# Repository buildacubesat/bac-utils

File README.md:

# bac-utils

Build a CubeSat – the utilities that keep the project running: KiCad release and library tooling, antenna simulation, Blender video editing helpers, media conversion, content and resource pipelines, repository checks, and the business operations suite. Every tool follows the [BAC Project & Tooling Guide](https://buildacubesat.space) and the BAC Interface Design Guide, so they look and behave alike: the same flags, the same terminal output, the same config locations.

The repository holds the generally usable state of each tool. Anything specific to one project – vendor prices, sheet IDs, repository paths, plugin locations – lives in your own config and data directories, created by each tool's `--init`. What ships here is the tool, sample data under `examples/`, and an `.env.example` where secrets are involved. See §6 to adapt a tool for your own project.

## 1. Tools

This table is the record of what exists, what is being worked on and what is planned; an available tool's name links to its directory: **available** has a tool directory, tests and a version; **in progress** has a directory on a branch or a concept note and work under way; **planned** has a decided home here and nothing built yet. Tools are listed by name within their group: libraries, command-line tools (with the one Tk window and the gallery), notebooks, the web app, the operations suite, the Blender extension.

| Tool | Type | Domain | What it does | Status | Version |
| :-- | :-- | :-- | :-- | :-- | :-- |
| [`bac-common`](lib/bac-common/) | library | CLI scaffold | Shared CLI scaffold: standard flags, TOML config, `.env` loading, `--init` helpers, the BAC terminal profile, error boundary, span-preserving s-expression parser, STEP header metadata, the part-catalog reader and resolver, Google Sheets reader (`gsheets` extra), test harness | available | v0.5.0 |
| [`bac-kicad-common`](lib/bac-kicad-common/) | library | KiCad | Shared KiCad library tooling: TOML field rules, property rendering for KiCad 9 and 10, span edits, write-back with backup | available | v0.1.0 |
| [`bac-suite-db`](lib/bac-suite-db/) | library | ops | Shared PostgreSQL layer of the operations suite: `bac.items` and `bac.catalog`, bootstrap config and the DSN in `.env`, the SKU scheme as a parser, an engine registry, the `bac-db` command (migrate, import, export, status) | available | v0.1.1 |
| [`bac-antenna-optimizer`](tools/bac-antenna-optimizer/) | CLI | RF | Antenna design around openEMS: parametric geometry, meshing rules, band targets, cavity-model pre-tuner, tolerance sweeps, sensitivity packs, reports with drawings, charts and KiCad board files | available | v0.7.5 |
| [`bac-brand-assets`](tools/bac-brand-assets/) | CLI | design | The construction of the BAC marks – the isometric cube symbol, the Nunito wordmark, the horizontal logo – and the generator that writes them as black, white and `currentColor` SVG into bac-design's `assets/`, with the trademark notice in every file, plus the tagline logo, the badges and the Rocinante marks, and their PNG and WebP renderings; `--check` in CI | available | v0.2.0 |
| [`bac-cad-preview`](tools/bac-cad-preview/) | CLI | CAD | Renders STEP, STL and 3MF files to 720 px WebP previews framed like the KiCad artifacts render, with an X/Y/Z scale gizmo; the preview stage of the planned `bac-freecad-generate-artifacts` | available | v0.5.1 |
| [`bac-can-up`](tools/bac-can-up/) | CLI | bench | Brings up the CANable SLCAN interface: fresh `slcand`, bitrate, `can0` up | available | v1.2.0 |
| `bac-catalog` | CLI | store | Builds the static part catalog the builder reads from the `part.toml` files next to the hardware designs | planned | – |
| [`bac-convention-check`](tools/bac-convention-check/) | CLI | repo | Lints a tree against the BAC guides (typography, naming, licensing, packaging, flags); runs in this repository's CI | available | v0.2.2 |
| [`bac-csr-ingest`](tools/bac-csr-ingest/) | CLI | resources | Ingests documents and links into the CubeSat Resources site: extraction, LLM classification, review, upload, index, commit | available | v0.4.1 |
| [`bac-design-export`](tools/bac-design-export/) | CLI | design | Exports the BAC guides in bac-design from Markdown to PDF as BAC documents (Identity Guide §7.3): markdown-it and WeasyPrint, the tokens straight from `bac-design-tokens`, the self-hosted fonts, A4 or Letter, contents and running header and footer; `--check` compares a source hash in each PDF, `--format html` shows the page in a browser |
| [`bac-design-tokens`](tools/bac-design-tokens/) | CLI | design | The canonical BAC design tokens (`tokens.json`, W3C design-tokens format) and the generator that writes every copy from them: the gallery's and the suite's `tokens.css`, the Rich colours in `bac-common`, the marimo style cells and chart constants; `--check` in CI | available | v0.1.0 |
| `bac-freecad-generate-artifacts` | CLI | CAD | FreeCAD counterpart of the KiCad artifacts tool: exports the file types and iterations of a part through the FreeCAD CLI, renders previews (absorbs `bac-cad-preview`), fills missing author, organisation and part metadata in STEP and 3MF output | planned | – |
| [`bac-issue-print`](tools/bac-issue-print/) | CLI | repo | Prints a Codeberg issue or pull request with its whole timeline – comments, reviews, pushes, references – as Markdown | available | v0.2.0 |
| [`bac-kicad-generate-artifacts`](tools/bac-kicad-generate-artifacts/) | CLI | KiCad | Produces the release bundle for a KiCad project through kicad-cli: render, pinout, schematic PDF, BOM – thin or legacy scheme; with the part catalogs configured also dev and flight build BOMs, a JLCPCB assembly file and an issues list –, iBOM, a frozen project with one build's parts written in, Gerbers, drills, centroid, STEP with header metadata, QR code on a copy of the board, manufacturing ZIP; panels without a schematic | available | v0.8.0 |
| [`bac-kicad-hlabels`](tools/bac-kicad-hlabels/) | CLI | KiCad | Emits hierarchical-label blocks for a list of net names, ready to paste into a schematic | available | v0.1.0 |
| [`bac-kicad-libcheck`](tools/bac-kicad-libcheck/) | CLI | KiCad | Verifies a library project: every symbol and footprint placed once, 3D models resolvable, in sync per KiCad's ERC/DRC | available | v0.2.0 |
| [`bac-kicad-maintain`](tools/bac-kicad-maintain/) | CLI | KiCad | Project files on the conventions: text and courtyard sizes on boards, via resizing, schematic label sizes, the title block's company, library nickname renames, size statistics; the library audit – unused footprints and models, broken links, field mismatches – with `#unused-` prefixing; the catalog check with the README tables regenerated | available | v1.4.1 |
| [`bac-kicad-schfields`](tools/bac-kicad-schfields/) | CLI | KiCad | Bulk-edits symbol fields and flags across a schematic hierarchy from TOML rules | available | v0.2.1 |
| [`bac-kicad-stitch`](tools/bac-kicad-stitch/) | CLI | KiCad | Ground stitching vias where a board's ground copper is too far from one: coverage by pitch or frequency, every spot checked against copper, holes, edge and courtyards on all layers, vias added by span in a `bac-stitch` group, preview SVG, DRC afterwards | available | v0.1.1 |
| [`bac-kicad-symfields`](tools/bac-kicad-symfields/) | CLI | KiCad | Fills fields, lints and fixes text sizes and footprint references in symbol and footprint libraries, preserving file formatting | available | v0.3.1 |
| [`bac-markdown-to-youtube`](tools/bac-markdown-to-youtube/) | CLI | content | Converts Markdown to YouTube description markup | available | v0.2.0 |
| [`bac-media-convert`](tools/bac-media-convert/) | CLI | media | Batch conversions: square WebP for the store, constant-frame-rate MP4 from variable-rate WebM | available | v0.1.1 |
| [`bac-page`](tools/bac-page/) | CLI | web | Creates and manages bac.page short URLs: a redirect folder per slug in the Pages repository, committed and pushed; `list`, `edit` (slug, destination), QR codes in SVG, PNG or WebP; a renamed slug stays as an alias of the new one | available | v0.6.0 |
| [`bac-reference-gallery`](tools/bac-reference-gallery/) | CLI and pages | design | Seven design-reference boards for the three BAC guides (identity, Ops and Mission, documents, interface patterns, charts, hardware, a product sheet) in light and dark, `tokens.css` (written by `bac-design-tokens`) as the stylesheet they are built on, a renderer to PNG and PDF through a headless Chromium, and `--serve` to show the pages in any browser | available | v0.5.0 |
| [`bac-store-product-cropper`](tools/bac-store-product-cropper/) | Tk GUI | media | Framing product photos for the store by hand, one window per batch, each crop exported as WebP under a size target; may later fold into a store artifact-generation tool | available | v0.2.1 |
| [`bac-update-content-plan`](tools/bac-update-content-plan/) | CLI | content | Renders the content plan from a Google Sheet into the docs repository as one Markdown table; commits and pushes on request | available | v0.4.1 |
| [`bac-antenna-visualizer`](notebooks/bac-antenna-visualizer/) | marimo notebook | RF | A slider per geometry parameter over an optimizer sensitivity pack: S-parameters, Smith chart, gain and axial ratio, pattern cuts, 3D pattern and fields; runs locally, with a frozen demo snapshot under `demo/` that runs in the browser from the repository and fetches its packs there | available | v0.3.8 |
| `bac-battery-pack` | marimo notebook | power | Battery pack configuration (cell, S × P, depth of discharge, temperature) and aging: cycle and calendar capacity fade over the mission, usable energy at end of life, the pack figures the power budget takes | planned | – |
| [`bac-link-budget`](notebooks/bac-link-budget/) | marimo notebook | RF | Link budget for a CubeSat radio link: passes, margins, data volume per day, validated against the AMSAT/IARU link model and SGP4 | available | v0.7.7 |
| [`bac-optical-payload`](notebooks/bac-optical-payload/) | marimo notebook | optics | Earth-observation and boom-camera optics: GSD, swath, smear, access and illumination over a target, days to downlink | available | v0.7.7 |
| `bac-orbit-viewer` | marimo notebook | orbit | 3D view of a mission's geometry around the globe from any sibling's profile | planned | – |
| [`bac-orbital-lifetime`](notebooks/bac-orbital-lifetime/) | marimo notebook | orbit | Decay under drag with NRLMSIS 2.1 and ten solar-activity scenarios; lifetime against launch date; disposal rules | available | v0.2.8 |
| [`bac-power-budget`](notebooks/bac-power-budget/) | marimo notebook | power | Generation, storage and loads over the orbit with a scheduler and safe mode | available | v0.5.7 |
| `bac-pv-aging` | marimo notebook | power | Single-diode model of a solar cell string fitted to datasheet points and aged over the mission by UV, atomic oxygen, displacement damage and thermal cycling: BOL and EOL IV curves, the EOL power factor the power budget takes | planned | – |
| `bac-thermal` | marimo notebook | thermal | Lumped-parameter thermal model of the spacecraft over the orbit, hot and cold cases, battery heater energy | planned | – |
| `bac-builder` | web app | store | Web app to configure a CubeSat build from BAC parts with a 3D view, tied to the store's prices and stock; cart, quote, CSV and PDF outputs; mass, power and data budgets per build | planned | – |
| [`bac-pricing`](ops/bac-pricing/) | marimo notebook | ops | Assembly pricing: multi-level BOM cost rollup and batch-waterfall price derivation as a pure engine, the notebook over it, the `pricing` schema of the operations suite; `bac-pricing` opens the notebook on the configured backend | available | v1.4.3 |
| [`bac-suite`](ops/bac-suite/) | CLI | ops | The operations suite's orchestrated shell: one web app with every installed engine's notebook behind a common index | available | v0.2.2 |
| [`bac-vse-tools`](blender/bac-vse-tools/) | Blender extension | video | One extension with three sub-panels in the VSE sidebar: bulk import of a folder of clips end to end, proxies built one strip at a time, meta strips separated with their trim kept | available | v1.0.0 |

The guides the tools follow – Identity, Interface Design, Project & Tooling and the Trademark Policy – live in [bac-design](https://github.com/buildacubesat/bac-design).

## 2. Install

Each tool is its own `uv` project and installs independently:

```sh
uv tool install ./tools/bac-issue-print
bac-issue-print --init
```

Tools that build on `bac-common` install from the checkout, not from PyPI; after pulling a new version, `uv tool install --force --reinstall ./tools/<name>` replaces the installed one. A tool with an optional extra takes it in the path: `uv tool install './tools/bac-cad-preview[step]'`. The suite's command-line tools install together – `uv tool install ./lib/bac-suite-db --with ./ops/bac-pricing` gives `bac-db` with the pricing engine – and `ops/README.md` describes the group. The reference gallery renders through a headless Chromium; `bac-reference-gallery --init` finds one or downloads Playwright's, and `bac-reference-gallery --serve` shows the pages in your browser (a Flatpak or Snap browser cannot open them from disk with their folder). The antenna optimizer runs inside the workspace environment because it needs the openEMS bindings (its README has the setup), and the notebooks run through marimo (§3).

The Blender extension is installed from a zip of `blender/bac-vse-tools/src/bac_vse_tools/` through Preferences → Get Extensions → Install from Disk; its README has the two ways to build the zip.

To work on the repository itself:

```sh
uv sync --all-packages
uv run pytest
uv run ruff check .
```

## 3. Notebooks

The engineering notebooks under `notebooks/` – link budget, optical payload, power budget, orbital lifetime, and the local-only antenna visualizer (with a frozen demo snapshot that runs on molab) – are single marimo files with PEP 723 metadata. Run one in its own environment with `uvx marimo edit --sandbox notebooks/bac-link-budget/bac_link_budget.py`, or in the workspace environment with `uv run marimo edit <file>`. The four published ones are the files behind the bac.page links, which open them from this repository's `main` – `bac.page/molab-<tool>-app` in app mode on marimo.app, ready to use, `bac.page/molab-<tool>` as a notebook in molab's editor – so a merge publishes; each of them carries the shipped profiles as TOML files under `examples/` and headless regression tests. The BAC profiles assume the 500 km planning orbit. `notebooks/README.md` has the rules of the class.

## 4. Layout

```
lib/       shared libraries (bac-common, bac-kicad-common, bac-suite-db)
notebooks/ engineering notebooks (marimo, single files, published for the community)
tools/     one directory per CLI tool, installable with uv tool install; the antenna optimizer's
           simulation output (runs/) stays out of git and the kept runs live in bac-hardware
ops/       business operations suite (Marimo notebooks + PostgreSQL)
blender/   Blender extensions
```

Every tool directory has the same shape: `pyproject.toml`, `src/bac_<name>/cli.py`, `README.md` with a version history, `tests/`, and where the tool consumes data, `examples/`. The reference gallery adds its pages beside them (`index.html`, `css/`, `assets/`, `examples/`), and the wheel carries them inside the package.

## 5. Conventions

Every CLI tool built on `bac-common` prints `<tool> vX.Y.Z` for `-v/--version`, accepts a hidden `--debug` that shows tracebacks, and keeps `--help` within 48 lines (24 until 2026-11-05) including two or three examples (at the end; the older Typer tools – `bac-csr-ingest`, `bac-kicad-symfields`, `bac-media-convert` – still print them above the options). The other standard flags appear where they apply: `--dry-run` where a run writes or changes something (on the subcommand that does, for the tools with subcommands), `--init` where the tool has a first-time setup – settings to write, or a browser to fetch for the reference gallery – and `--config PATH` where it keeps persistent settings, `--env-file PATH` where it reads secrets or machine-specific values, `-l/--list` where it works on a named set. Filters that write to stdout (`bac-markdown-to-youtube`, `bac-kicad-hlabels`) and read-only tools (`bac-convention-check`) have no `--dry-run`. Each tool's README lists its flags. Since 0.7.5 the antenna optimizer's command line is on `bac-common` too (it predated the scaffold); its subcommands keep their own plain tables. The notebooks are exempt from the flags and carry their version in `TOOL_VERSION` and in every export's header.

Config lives at `~/.config/bac/<tool>.toml`; secrets in a `.env` file loaded with python-dotenv. Exit codes are 0 for success, 1 for a runtime error, 2 for bad arguments. Errors go to stderr; tracebacks appear only with `--debug`. Terminal output uses the BAC Interface Design Guide's terminal profile through `bac_common.ui`. Colours, type and form come from one place, `tools/bac-design-tokens/src/bac_design_tokens/tokens.json`: `bac-design-tokens` writes them into the gallery's and the suite's `tokens.css`, the Rich colours and the notebooks' style cells, and its tests fail when a copy is stale.

Software in this repository is licensed MIT (see `LICENSE`); documentation CC BY-SA 4.0. The design tokens (`tokens.json`) and the reference gallery's stylesheets are both – MIT or CC BY-SA 4.0, at your option – so any software, BAC Ground included, can take the values. The Build a CubeSat name and logo are not covered by this repository's licenses; see the [BAC Trademark Policy](https://github.com/buildacubesat/bac-design/blob/main/guides/bac-trademark-policy.md). Software versions follow SemVer and display with a `v` prefix.

## 6. Adapting for your own project

Run `<tool> --init`. It asks for the paths, identifiers and endpoints the tool needs, writes `~/.config/bac/<tool>.toml`, and where secrets are involved, a `.env` next to your working directory with empty values to fill in. Tools that consume data files take a data directory from that config; the copies under each tool's `examples/` show the expected shape and can be copied as a starting point. Nothing in the repository needs editing to point a tool at your own project.

## 7. Version history

| Version | Date | Change |
| :-- | :-- | :-- |
| 0.24.1 | 2026-11-06 | `bac-kicad-maintain` v1.4.1: the audit compares `Description` only for symbols that name a part, and a live symbol nothing places is not reported when a catalog row names its part. |
| 0.24.0 | 2026-11-05 | `bac-kicad-generate-artifacts` v0.8.0: the BOM scheme (`thin` default, `legacy` for projects whose symbols carry their part data – no catalog, `--bom-scheme`), the `Build` and `Qty per footprint` fields, the `freeze` stage (`--freeze dev|flight` writes `<project>-frozen-<build>/` with the resolved part numbers in every symbol and footprint, DNP on build-excluded parts, `FROZEN.md`), the iBOM on KiCad's DNP attribute. `bac-common` v0.5.0: `bac_common.catalog` (the reader and resolver moved from the artifacts tool, the third collection named `other`, `check()` and the README tables) and the help limit at 48 lines. `bac-kicad-maintain` v1.4.0: `check`/`apply --catalog` (findings on the catalog CSVs, the ICs-shaped READMEs regenerated), `[audit] catalogs` on `resources/catalog/`. `bac-kicad-symfields` v0.3.1 and `bac-kicad-schfields` v0.2.1: the example rules retired as the BAC workflow. |
| 0.23.0 | 2026-11-05 | `bac-kicad-maintain` v1.3.0: the library audit as `check`/`apply --audit` over a repository root – the central library, every board, sheet, template and design block, the catalog CSVs – reporting unused footprints and 3D models (the usage rule of 2026-10-29), broken links with `#unused` hints, field mismatches and unplaced symbols; `apply` prefixes unused files `#unused-` and lets the references in unused symbols and footprints follow. `--titleblock` sets the title block's company (`nihil.space GmbH`) on boards and sheets. `uv.lock` caught up with `bac-reference-gallery` 0.5.2. |
| 0.22.0 | 2026-10-29 | New `bac-design-export` v0.1.0: the guide PDFs in bac-design `exports/` built Markdown → HTML → PDF as BAC documents, per the new Identity Guide §7.3 – the tokens from `bac-design-tokens` (no copy), static Nunito Sans instances cut from the variable font and IBM Plex Mono embedded, a BAC Symbols face for the arrows and box drawing Nunito Sans lacks, contents with page numbers, `--check` by source hash. Replaces the pandoc → docx → LibreOffice route. `bac-convention-check` v0.2.3: U1 allows `bac-design` and `bac-ops` on GitHub. `bac-reference-gallery` v0.5.1: the slogan "Space for everyone." on the identity overview. `bac-brand-assets` templates: the slides template v1r2 on the Mission surfaces of the Tooldance media kit (`nebula.jpg`, paper wells, timeline, quote); `surfaces.py` renders the viewport only. |
| 0.21.0 | 2026-10-29 | `bac-page` v0.6.0: a rename leaves the old slug redirecting to the new short URL, marked as renamed in its `index.html`; `list` dims these aliases and `list --old` shows only them; `edit` and `add` leave them alone. The legacy `~/.config/bac-page/.env` is no longer read. |
| 0.20.2 | 2026-10-29 | `bac-kicad-generate-artifacts` v0.7.2: a part the catalog marks `accepted` – no qualified variant, fitted to flight builds by decision – stays in the flight build like a qualified one; `aec-q102` counts as qualified. |
| 0.20.1 | 2026-10-28 | `bac-kicad-generate-artifacts` v0.7.1: a third catalog folder, `parts`, for connectors, switches, LEDs and the like (the ICs' columns and rules); from the first live BOM of the MCU carrier, where every passive and IC resolved. |
| 0.20.0 | 2026-10-28 | `bac-kicad-generate-artifacts` v0.7.0: the `bom` stage resolves the schematic against the Build a CubeSat part catalogs (`bac-hardware/resources/`, named in `[catalog]`) – passives by value and package, ICs by manufacturer part number through their slot's flight candidate and its compatibility – and writes `…-bom-dev.csv`, `…-bom-flight.csv`, `…-bom-jlcpcb.csv` and `…-bom-issues.csv` next to the plain export; the schematic stays thin. Without `[catalog]` nothing changes. |
| 0.19.0 | 2026-10-28 | `bac-page` v0.5.0 moves in from the Pages repository's `cli/` as `tools/bac-page` on `bac-common`: the standard parser and error boundary, opening panel and summary, the shared config loader, 36 tests on a throwaway repository with a bare remote; commands, slugs, redirect files, QR options and git behaviour unchanged (a malformed slug or target exits 2 now, a subcommand's `--help` reaches the subcommand). The legacy `~/.config/bac-page/.env` is read with a note until 0.6. |
| 0.18.0 | 2026-10-27 | `bac-brand-assets` v0.2.0 (0.1.0 the same day): the BAC marks at v4r1 as a construction – the symbol a true 30° isometric 2U cube (edge 200, stroke 15, rounded corners, the dot in the 1:√3 projection ratio) on a 400 × 650 canvas, the wordmark Nunito 350 outlined with fontTools, the logo the horizontal lockup at 70 % of the cube height – written as black, white and `currentColor` SVG with title, desc and Dublin Core metadata into bac-design's `assets/`, from the Nunito that bac-design now self-hosts in `fonts/`; `--check` for CI; the logo with tagline, the symbol and logo badges, and the Rocinante marks at v2r1 from the Krita vector layers, with PNG and WebP renderings at 512 and 2048 px. The v3r1 symbol was a bitmap trace. |
| 0.17.0 | 2026-10-27 | Design 1.0: the BAC guides move to the BAC Ground console language (Identity Guide 1.0, Interface Design Guide 1.0, Project & Tooling Guide 0.15), and the tokens get one source. New `bac-design-tokens` v0.1.0: `tokens.json` and the generator for the gallery's and the suite's `tokens.css`, the Rich colours in `bac-common` and the marimo style cells and chart constants, with `--check` in its tests. `bac-reference-gallery` v0.5.0: every board on the new tokens and component language (Nunito Sans body, mono labels at 0.03em, pills, no shadows, the five states with shapes, the neutral dark-mode accent, the nebula triad). `bac-common` v0.4.2: success `#3FB950`, error `#E94538`. `bac-suite` v0.2.2: the index page on the new tokens. Notebooks – Nunito Sans body, the console surfaces and the shared chart palette, no number changes: `bac-link-budget` v0.7.7, `bac-optical-payload` v0.7.7, `bac-power-budget` v0.5.7, `bac-orbital-lifetime` v0.2.8, `bac-antenna-visualizer` v0.3.8 (demo re-snapshotted), `bac-pricing` v1.4.3 (no price changes). Colour constants on the new palette: `bac-store-product-cropper` v0.2.1, `bac-kicad-stitch` v0.1.1, `bac-cad-preview` v0.5.1. |
| 0.16.2 | 2026-10-24 | The notebooks' chart colors under marimo's "system" theme: chart text, axis lines and ticks no longer carry explicit colors – marimo hands the chart its dark theme on a dark surface and Vega's defaults apply on a light one – and the series palette is one set, the lighter nebula tints that read on a dark surface too; the style cell's `.vega-embed text` rule is gone (the charts render on canvas inside a shadow root). `bac-link-budget` v0.7.6, `bac-optical-payload` v0.7.6, `bac-power-budget` v0.5.6, `bac-orbital-lifetime` v0.2.7, `bac-antenna-visualizer` v0.3.7 (demo re-snapshotted), `bac-pricing` v1.4.2; no number changes. |
| 0.16.1 | 2026-10-24 | The follow-ups batch 1 left open. `bac-antenna-optimizer` v0.7.5: the command line on `bac-common` – `-v` prints `bac-antenna v0.7.5`, hidden `--debug`, the error boundary, `--help` within 24 lines with examples; subcommands and output unchanged. `bac-csr-ingest` v0.4.1 runs its Typer app through `run_typer` (usage errors exit 2, Ctrl-C prints `Interrupted.`). `bac-suite-db` v0.1.1: `bac-db import` on the `files` backend validates and stops with a note instead of asking for a database. `bac-kicad-generate-artifacts` v0.6.2: the `--qr` example names the live short link. `bac-convention-check` v0.2.2 knows the Pages repository's new name. CI installs Playwright's Chromium so the gallery's browser tests run, and a second workflow runs the Blender tests with the `bpy` wheel when `blender/` changes. The Pages repository is [`bac-page`](https://github.com/buildacubesat/bac-page) now; the dead `molab-antenna-viz-demo` link in the visualizer's history unlinked. |
| 0.16.0 | 2026-10-19 | `bac-kicad-stitch` v0.1.0: ground stitching vias from the filled ground zones – the pitch given or derived from a frequency, coverage instead of a via count, every candidate checked on all copper layers, farthest-point placement, the vias in a `bac-stitch` group that `remove` takes out again, a preview SVG, `kicad-cli pcb drc` after writing. |
| 0.15.2 | 2026-10-13 | `bac-issue-print` v0.2.0: the timeline instead of the plain comments – reviews with their line comments, pushes, references, title changes and the rest of what the issue page shows; `--comments-only` for the old output. |
| 0.15.1 | 2026-10-13 | `bac-issue-print` v0.1.1: the comments come in one request – the Forgejo endpoint is not paginated and 0.1.0's page walk never ended. |
| 0.15.0 | 2026-10-12 | `bac-kicad-maintain` v1.2.0, the last batch-1 tool: text, courtyard and via sizes on boards, label sizes on schematics, `stats` and `rename-library`, folded in on `bac-common` and `bac-kicad-common` with `.bak` backups, a confirmation before writing and edits that follow KiCad's line layout; boards and schematics only, footprint libraries stay with `bac-kicad-symfields fix`. |
| 0.14.1 | 2026-10-12 | The notebooks' bac.page links: two per tool, `bac.page/molab-<tool>-app` (app mode on marimo.app, ready to use) and `bac.page/molab-<tool>` (a notebook in molab's editor), both reading the file from this repository's `main` – the molab copies are gone, a merge publishes. Every intro links both; `bac-link-budget` v0.7.5, `bac-optical-payload` v0.7.5 (its short link is `molab-optical-pld` now), `bac-power-budget` v0.5.5, `bac-orbital-lifetime` v0.2.6, `bac-antenna-visualizer` v0.3.6 (the demo's short link is `molab-antenna-viz`; demo re-snapshotted). No number changes. |
| 0.14.0 | 2026-10-09 | `bac-reference-gallery` v0.4.0: `--serve` shows the gallery over `http://127.0.0.1` in any browser – opened from disk, `index.html` came up without its stylesheets and previews in a Flatpak browser, which receives a local file without its folder – and the stylesheets are dual-licensed, MIT or CC BY-SA 4.0. The notebooks' glossary links checked against the CubeSat Resources glossary (two anchors that did not exist fixed, the power rails off the deployer-rail entry, first-use links in all five) and their muted grey moved to the AA values of the shared tokens: `bac-link-budget` v0.7.4, `bac-optical-payload` v0.7.4 (its assumptions name both readings of Q, Holst's for resolution and Nyquist sampling at Q = 2, as the glossary does), `bac-power-budget` v0.5.4, `bac-orbital-lifetime` v0.2.5, `bac-antenna-visualizer` v0.3.5, and `bac-pricing` v1.4.1 for the grey; no number changes. `bac-suite` v0.2.1: the index page links `tokens.css` instead of carrying its own colours. `/tmp/` at the checkout root is ignored. |
| 0.13.0 | 2026-10-08 | `bac-reference-gallery` v0.3.0 joins on `bac-common`: the seven boards in light and dark with every colour through `tokens.css`, now the shared stylesheet and a full copy of the Identity Guide's tokens with AA-safe `--text-muted` and `--link`; every text on every board passes WCAG AA in both modes, with focus rings, reduced motion, `lang`, table scopes and labelled form controls; the product sheet without price and contact data; the renderer as `bac-reference-gallery` with `--out-dir`, `--theme`, `--source`, the pages inside the package and `--init` for the browser. `bac-common` v0.4.1 and `bac-update-content-plan` v0.4.1: the service-account key's path says where it came from. Final README pass: the tool table grouped and ordered as its intro says, §2 on installing every kind of tool, §5 states the standard flags that apply instead of claiming all of them everywhere; the notebooks' `pyproject.toml` versions follow their `TOOL_VERSION` (notebooks 0.13.0); the `bac-convention-check` row says v0.2.1 again (it read v0.2.2 since 0.8.3, a typo). The LICENSE names nihil.space GmbH and the Build a CubeSat contributors as copyright holders. |
| 0.12.0 | 2026-10-07 | `bac-vse-tools` v1.0.0: the three Blender add-ons as one extension under `blender/` with a manifest, three panels under VSE Tools and settings in a property group on the scene; Bulk Import no longer saves the open file and keeps its copies out of the media folder (autosave opt-in, confirmed) and keeps Blender's A/V sync through the Add Movie operator, the proxy build runs as a background job with a timeout over the whole wait and stale proxies ignored, Separate Meta asks before removing strips. Tested headless inside Blender 4.5 through the `bpy` wheel; `blender/` joins ruff and pytest. |
| 0.11.0 | 2026-10-07 | `bac-update-content-plan` v0.4.0 rewritten on `bac-common` (sheet, range, repository and branch in `~/.config/bac/`, the repository validated before the sheet is fetched, pipes escaped, the commit limited to the file, confirmation before `git push`, `--dry-run` reports what would change) and `bac-store-product-cropper` v0.2.0 repackaged under its new name (the double-Enter save, the stretched preview, the quality-order crash and the double listing fixed; `--out-dir`, collision check, skip of existing outputs). `bac-common` v0.4.0 adds `bac_common.gsheets` behind the `gsheets` extra. `bac-media-convert` v0.1.1: "the store" replaces "the shop" here and in its own text; the planned `bac-builder` and `bac-catalog` rows follow. |
| 0.10.0 | 2026-10-07 | The business operations suite joins under `ops/`: `bac-suite-db` v0.1.0 (the shared PostgreSQL layer lifted from bac-pricing's `bac_store.py`, `bac-db` on `bac-common`, the DSN in `.env` and redacted everywhere, the SKU scheme as a parser), `bac-pricing` v1.4.0 (engine, store and notebook as a package with the `bac-pricing` launcher, the data files as `examples/` with the three SKUs migrated to the guide scheme, the notebook on the shared style cell with one control panel, validation on import, the parity test as pytest with a guarded live variant) and `bac-suite` v0.2.0 (engines found through entry points). The SQL was run against PostgreSQL 16 before release and the live tests keep doing so with `BAC_TEST_DSN`; `ops/README.md` describes the group. |
| 0.9.1 | 2026-10-07 | `bac-kicad-generate-artifacts` v0.6.1: the output folder carries the full artifact name (`bac-inhibit-deployment-switch-v1r1/`), fixes from the first live run (absolute paths for the iBOM plugin, program lookup at call time, `--init` text). |
| 0.9.0 | 2026-10-06 | `bac-kicad-generate-artifacts` v0.6.0 joins on `bac-common`: the 0.5.0 stage architecture with the installed 0.4.2's behaviour, the live-run bugs of 2026-10-02 fixed (names from the project stem, no doubled prefix, no spaces in Gerber names, `.gbrjob` rewritten), a QR stage on `bac_common.sexp` after Emil Fresk's kicad-qr-inserter, STEP header metadata through the new `bac_common.cad` (`bac-common` v0.3.0), kicad-cli 10 targeted directly; the deployment switch and a synthetic project as fixtures. |
| 0.8.5 | 2026-10-06 | The notebooks' bac.page links are the molab short links (`bac.page/molab-<tool>`, the demo at `molab-antenna-viz-demo`); five patch bumps. |
| 0.8.4 | 2026-10-06 | `bac-orbital-lifetime` v0.2.3: the "Solar Activity Assumed" chart drew nothing in the browser since 0.1.0 (a dot in the data column name is nested access to Vega-Lite). The visualizer demo fetches its two S-band packs from `notebooks/bac-antenna-visualizer/demo/packs/` (now tracked) when none sit beside it, so a molab mirror of the file works as is. |
| 0.8.3 | 2026-10-06 | Chart titles that Altair clipped are split into title and subtitle in the five notebooks (`chart_title` in the shared chart-conventions cell): `bac-link-budget` v0.7.2, `bac-optical-payload` v0.7.2, `bac-power-budget` v0.5.2, `bac-orbital-lifetime` v0.2.2, `bac-antenna-visualizer` v0.3.3. The tool table gains a Type column and links every available tool to its directory. |
| 0.8.2 | 2026-10-06 | The BAC planning orbit moves to 500 km (was 450 km): `bac-link-budget` v0.7.1, `bac-optical-payload` v0.7.1, `bac-power-budget` v0.5.1 and `bac-orbital-lifetime` v0.2.1 with their profiles, panel defaults, regression figures and READMEs; the lifetime takes the siblings' chart-conventions and style cells; the four notebooks are formatted and linted by ruff from now on (exemptions dropped, F841 added for cell globals). |
| 0.8.1 | 2026-10-06 | `bac-antenna-visualizer`: a demo snapshot for molab under `notebooks/bac-antenna-visualizer/demo/` – the visualizer without the optimizer, geometry from the pack's stored models, packs found beside the file – with its own headless tests; the demo is covered by `marimo check` in CI. |
| 0.8.0 | 2026-10-02 | The `notebooks/` group: `bac-link-budget` v0.7.0, `bac-optical-payload` v0.7.0, `bac-power-budget` v0.5.0 and `bac-orbital-lifetime` v0.2.0 come in as byte-identical copies of the published files with example profiles and regression tests from their handoffs; `bac-antenna-visualizer` v0.3.2 moves there from `tools/`; a shared headless harness; `marimo check` and the notebook tests in CI. `bac-convention-check` v0.2.1 stops flagging a notebook's build-system-less pyproject. |
| 0.7.0 | 2026-10-02 | `bac-cad-preview` v0.5.0 joins on `bac-common`: STEP, STL and 3MF previews framed like the KiCad artifacts render, faces named with the project's axis letters, `--out-dir`, output collisions refused; the `step` extra carries OpenCascade. |
| 0.6.0 | 2026-10-02 | The two antenna tools from the S-band sessions brought in: `bac-antenna-optimizer` v0.7.4 (tag `bac-antenna-optimizer-v0.7.3` marks the version that generated the S-band cross patch in bac-hardware) and `bac-antenna-visualizer` v0.3.1, both on the conventions; the root `.gitignore` takes over their ignore rules. `bac-common` v0.2.1 and a root `conftest.py` pin the terminal widths under test, so the suite passes at any width (five tests failed at 80 columns before). The tool table becomes the tracking view of everything planned for the repository. |
| 0.5.0 | 2026-09-07 | The KiCad library tools and the CAN bench tool: `bac-kicad-symfields` v0.3.0, `bac-kicad-schfields` v0.2.0 and `bac-kicad-libcheck` v0.2.0 folded in from the separate bac-kicad-tools repository (the four `bac-kicad-misc` lint scripts absorbed as `symfields lint` and `fix`), `bac-can-up` v1.2.0 ported from `canup.sh`. New `bac-kicad-common` v0.1.0; `bac-common` v0.2.0 adds `bac_common.sexp`. All batch-1 tools have now arrived. |
| 0.4.0 | 2026-09-04 | Four small tools on the scaffold: `bac-markdown-to-youtube` v0.2.0 (rewritten conversion), `bac-issue-print` v0.1.0 (ported from shell, pagination, token), `bac-kicad-hlabels` v0.1.0 (flags, `--gap-on-blank`), `bac-media-convert` v0.1.0 (`webp-square`, `cfr`; the two shell loops retired). `bac-common` v0.1.1: `.env` is searched from the working directory, `run_typer` puts Typer tools inside the error boundary. |
| 0.3.0 | 2026-09-02 | `bac-convention-check` v0.2.0 ported to Python with TOML rule sets; runs on the repository in CI. |
| 0.2.0 | 2026-09-02 | `bac-csr-ingest` v0.4.0: first tool on `bac-common`; classifier trust boundary, upload guard, phase order. Root pytest runs in importlib mode so tools may share test module names. |
| 0.1.0 | 2026-09-02 | Repository skeleton: uv workspace, CI, `bac-common` v0.1.0 lifted from the CSR Ingest reference implementation. Tools follow in the homogenization plan's order. |

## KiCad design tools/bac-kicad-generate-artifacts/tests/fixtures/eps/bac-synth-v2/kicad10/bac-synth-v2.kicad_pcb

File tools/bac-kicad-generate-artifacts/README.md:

# bac-kicad-generate-artifacts v0.8.0

Build a CubeSat – the release bundle of a KiCad project from one command. For every project folder given, the tool drives `kicad-cli` through the stages of a hardware release and puts the results into one folder: a 720 × 720 px 3D render, a 1920 × 1080 px pinout plot, the schematic PDF, the CSV BOM – with the part catalogs configured also a dev and a flight build BOM, a JLCPCB assembly file and an issues list –, an optional interactive HTML BOM, an optional frozen project with one build's parts written in, Gerbers and Excellon drills, the pick-and-place centroid file, the STEP model with author and organisation in its header, an optional QR code on the board, and a timestamped manufacturing ZIP. Every file is named after the BAC artifact scheme `<prefix>-<subsystem>-<name>-<vXrY>-<kind>.<ext>`, with the version and revision read from the board's title block.

Everything specific to a project – output root, naming prefix, author, BOM scheme and fields, part catalogs, plugin paths – lives in `~/.config/bac/bac-kicad-generate-artifacts.toml`, written by `--init`. The defaults are BAC's; §10 says what to change for another project.

## 1. Install

```sh
uv tool install ./tools/bac-kicad-generate-artifacts   # from the bac-utils checkout
bac-kicad-generate-artifacts --init
```

Programs on `PATH` at run time: `kicad-cli` from KiCad 10 (the stages are written against the 10.x command set and tested with 10.0.3; the tool does not probe the help text for older builds) and `inkscape` or `rsvg-convert` (librsvg) to rasterise the pinout plot. The WebP images are encoded by Pillow, so `cwebp` is no longer needed. Optional: a system `python3` that imports `pcbnew`, with the InteractiveHtmlBom plugin, for `--ibom`; `xdg-open`/`open` and `gerbview` for `--open`. The tool depends on `bac-common` from this repository, so it installs from the checkout, not from PyPI.

## 2. Usage

```
bac-kicad-generate-artifacts [options] KICAD_DIR [KICAD_DIR ...]
```

```sh
bac-kicad-generate-artifacts ~/bac/bac-hardware/inhibit/deployment-switch/kicad10
bac-kicad-generate-artifacts --ibom --qr https://bac.page/deployment-switch-v1 --open deployment-switch/kicad10
bac-kicad-generate-artifacts --dry-run --skip step panel-a/kicad10 panel-b/kicad10
bac-kicad-generate-artifacts --freeze flight --only freeze ~/bac/bac-hardware/eps/main-board/kicad10
bac-kicad-generate-artifacts --bom-scheme legacy ~/nihil.space/blackwing-cm5-payload-v1/design/kicad10
```

`KICAD_DIR` is the folder that holds the `.kicad_pro`, `.kicad_pcb` and `.kicad_sch` files. Several folders are processed in turn; one failing folder does not stop the others, and the summary (projects, done, failed) is printed on every path. Exit codes: `0` every project done, `1` at least one stage or project failed, or the config file is invalid, `2` bad arguments.

| Option | Effect |
| :-- | :-- |
| `--desktop DIR` | Output root. Default: `root` in the config, else `$XDG_DESKTOP_DIR` or `~/Desktop`. |
| `--only STAGES`, `--skip STAGES` | Run only, or run without, the named stages (comma-separated; §3 has the names). An unknown name exits 2 and lists them. |
| `--ibom` | Also build the interactive HTML BOM (opt-in: it needs KiCad's own Python). |
| `--qr TEXT` | Replace the `QR_MARKER` text boxes on the board with a QR code of `TEXT` (§6). |
| `--bom-scheme SCHEME` | `thin` (the default, and `scheme` in `[bom]`): the schematic carries value, footprint and manufacturer part number and the catalogs supply the rest (§5). `legacy`: the symbols carry manufacturer, package, tolerance and the rating fields themselves – the plain export gets those columns and no catalog is read (§5.3). |
| `--freeze BUILD` | Also write the frozen project of the `dev` or `flight` build next to the project folder (§5.2). |
| `--patch N` | Patch revision on the version tags: `v1r2` becomes `v1r2.N` for the board and the schematic. |
| `--open` | Open the output folder in the file manager and the ZIP in GerbView when the project is done. |
| `--dry-run` | Print the plan and record the commands (`--debug` shows them); nothing is written, not even the output folder. The QR stage only names its text, so the recorded board paths are the project's own. |
| `--config PATH`, `--init` | Another config file; first-time setup (§4). |

The run prints an opening panel, a rule per project with the board, title, revision, schematic and output folder, one `✓` line per stage with the file it wrote, its size and the time it took (`✗` with the reason when a stage fails, `·` for a skipped stage), and the summary. `--debug` adds every command that was run and keeps the `.work/` folder.

## 3. Stages

Stages run in this order; `--only` and `--skip` pick from them.

| Stage | Writes | Notes |
| :-- | :-- | :-- |
| `qr` | `.work/project/<board>.kicad_pcb` | Opt-in (`--qr TEXT` or `text` in `[qr]`). Copies the project folder into the work folder and replaces the marker boxes on the copy; the later board stages export from that copy. The project itself is never written. |
| `render` | `<base>-render.webp` | `kicad-cli pcb render` at 2160 × 2160 px, rotated 22.5°/−22.5°, zoom 0.8, side lights at 90°, transparent; cropped to the board, padded 10 %, squared and resized to 720 px, lossless WebP. `bac-cad-preview` frames its previews the same way. |
| `schematic` | `<sch-base>-schematic.pdf` | Black and white, all sheets. |
| `pinout` | `<base>-pinout.webp` | `Edge.Cuts`, `F.Fab` and `F.Silkscreen` as a single black-and-white SVG, rasterised at 4× and scaled to 80 % of a 1920 × 1080 px transparent canvas. |
| `bom` | `<sch-base>-bom.csv`, `…-bom-dev.csv`, `…-bom-flight.csv`, `…-bom-jlcpcb.csv`, `…-bom-issues.csv` | `kicad-cli sch export bom` with the scheme's columns (or the field list, labels and grouping from `[bom]`); a `Qty per footprint` field multiplies the quantity (§5.1). In the thin scheme with the part catalogs configured in `[catalog]` (passives, ICs, other), a second export (reference, quantity, value, footprint, `Manufacturer PN`, DNP, `Build`, `Qty per footprint`) is resolved against them and written as the dev and flight build BOMs, the JLCPCB assembly file and the issues list (§5). In the legacy scheme the plain export is all there is. |
| `ibom` | `<base>-ibom.html` | Opt-in (`--ibom`). Exports a `kicadxml` netlist and runs the InteractiveHtmlBom plugin (`script` in `[ibom]`) with the first Python that imports `pcbnew`: `python` in `[ibom]`, then `/usr/bin/python3`, then `python3`. Dark mode, pin 1 highlighted, KiCad's DNP attribute as the DNP source (the `BOM` field of 0.7 is gone from the library); the plugin's browser tab opens only with `--open`. The plugin takes a relative `--dest-dir` as relative to the board's folder, so it gets absolute paths. |
| `freeze` | `<project>-frozen-<build>/` next to the project folder | Opt-in (`--freeze dev` or `--freeze flight`); needs the thin scheme and the catalogs. Copies the project folder (backups, caches and lock files left out) and writes the build's resolved `Manufacturer PN`, `LCSC` and `Digikey` into every placed symbol and board footprint; a part the `Build` field keeps out of the build gets the DNP attribute; `FROZEN.md` and two title-block comments record build, date, catalog versions and source commit (§5.2). A folder of that name is replaced. |
| `gerbers` | `gerber/` | Into an emptied `gerber/`: the board's copper layers (read from its `(layers …)` block, in stack order) plus `F.Paste`, `B.Paste`, `F.Silkscreen`, `B.Silkscreen`, `F.Mask`, `B.Mask`, `Edge.Cuts`; on a panel also `User.Comments` (V-cut lines). RS-274X without X2 attributes, 6 digits, KiCad extensions. Zone fills are exported as saved: `--check-zones` is never passed, so a panel's fills stay as the panelizer left them and a board's fills are the ones its designer last filled. |
| `drills` | `drill/` | Into an emptied `drill/`: Excellon, absolute origin, millimetres, decimal format. |
| `centroid` | `centroid/<base>-centroid.pos` | ASCII, millimetres, both sides in one file, SMD only, DNP excluded, drill/place file origin. |
| `step` | `<base>-model.step` | `--subst-models --force`; then the STEP header's `FILE_NAME` entity gets the file's name, and `author` and `organization` from `[metadata]` replace the placeholders KiCad writes there (`Pcbnew`, `Kicad`) when they are set (`bac_common.cad`). |
| `zip` | `<base>-<YYYY-MM-DD-HH-MM>.zip` | Renames the Gerber and drill files from kicad-cli's `<board stem>-<layer>` to `<base>-<layer>`, rewrites the paths inside the `.gbrjob` job file to match, and zips `gerber/`, `drill/` and `centroid/`. The timestamp is UTC. Refuses when `gerbers`, `drills` or `centroid` failed in this run. |

`<base>` is `<prefix>-<subsystem>-<name>-<vXrY>` from the board's title block; `<sch-base>` carries the schematic's own tag, which differs only when the two title blocks disagree. Layer names in Gerber file names are KiCad's default names (`F_Cu`, `In1_Cu`, `F_Silkscreen`, `Edge_Cuts`): a layer the designer renamed in the board setup (`B.Cu MIX`) is mapped back to its default name, so a user layer name never puts a space into a Gerber file name. Two files that would get the same name are numbered `-2`, `-3`. A run into an output folder that exists replaces the render, plots and exports of the earlier run and adds its own ZIP; the earlier ZIPs stay.

A folder without a `.kicad_sch` file is a **panel**: the tool says so with a `!` line and proceeds; `schematic`, `pinout`, `bom`, `ibom` and `freeze` are skipped, `User.Comments` joins the Gerber layers, and the fills are exported as saved.

## 4. Names and the config file

The output folder is `<root>/<base>/`, so two projects of the same name in different subsystems never share a folder. The pieces of the scheme:

- **prefix** – `bac` (`prefix` in `[naming]`).
- **subsystem** – the folder below the hardware repository on the project's path: `.../bac-hardware/inhibit/deployment-switch/kicad10` gives `inhibit` (`hardware_root` in `[naming]` names the repository folder). A project outside that repository gets no subsystem and the prefix stands alone; so does a project folder that is the subsystem itself.
- **name** – the project's own kebab name: the `.kicad_pro` stem (or the board's) without the prefix and the trailing `-v<N>` token, so `bac-deployment-switch-v1` gives `deployment-switch` and the artifacts are `bac-inhibit-deployment-switch-v1r1-…`, never `bac-inhibit-bac-inhibit-…`. Without a usable stem the title block's title is slugified; the parent folder's name is the last resort.
- **vXrY** – the `v` token of the title block's title (`… v1`, `v1.2`) and the `rev` field normalised to `r<N>` (`1`, `r1`, `R 1` all give `r1`; other text becomes `r-<text>`); `--patch N` appends `.N`.

`--init` writes `~/.config/bac/bac-kicad-generate-artifacts.toml` with every key and its default, and finds the InteractiveHtmlBom plugin where KiCad's plugin manager installs it (Linux, Windows, macOS). It never overwrites an existing file. Every key is optional; the tool runs without the file.

```toml
[output]
root = ""              # empty: $XDG_DESKTOP_DIR or ~/Desktop; --desktop overrides
timeout_s = 600        # per command

[naming]
prefix = "bac"
hardware_root = "bac-hardware"

[metadata]
author = ""            # into the STEP header in place of KiCad's placeholders
organization = ""

[bom]
scheme = "thin"        # or "legacy" (§5.3); --bom-scheme overrides per run
fields = ""            # kicad-cli --fields / --labels / --group-by; empty: the scheme's columns
labels = ""
group_by = ""

[catalog]
passives = ""          # folder with bac-passives-capacitors.csv and bac-passives-resistors.csv (§5)
ics = ""               # folder with bac-ics.csv
other = ""             # folder with bac-other.csv (connectors, switches, LEDs – the ICs' columns); all empty: the plain export only

[ibom]
script = ""            # generate_interactive_bom.py; --init fills it in when the plugin is installed
python = ""            # empty: /usr/bin/python3, then python3

[qr]
marker = "QR_MARKER"
text = ""              # default for --qr; the stage runs whenever a text is known
```

## 5. Build BOMs from the part catalogs

The schematic stays thin: a passive carries `Value` and `Footprint`, an IC its `Manufacturer PN`; the plain `…-bom.csv` has exactly those columns (`Reference`, `Qty`, `Value`, `Footprint`, `Manufacturer PN`, `DNP`, `Build`, `Datasheet` – the templates' BOM preset). Which part is bought for a given build is the catalogs' business – the Build a CubeSat part collections in `bac-hardware/resources/catalog/`: `passives/bac-passives-capacitors.csv` and `passives/bac-passives-resistors.csv` with one row per value, package and grade (`dev` for the commercial part at LCSC, `flight` for the AEC-Q200 part), `ics/bac-ics.csv` with the parts of a board grouped in slots (one function in one footprint: the `reference` part fitted on the board, `drop-in` alternatives, the `flight` candidate), and `other/bac-other.csv` – connectors, switches, LEDs, holders, spacers, crystals, discretes – in the ICs' columns. `examples/catalog/` holds a few rows of each. The reader and the resolver live in `bac_common.catalog` since 0.8.0, so `bac-kicad-maintain check --catalog` checks the same files. Name the folders in `[catalog]` (any of the three may stay empty; the 0.7 key `parts` is still read for `other`, with a warning) and the `bom` stage writes, next to the plain export:

| File | Content |
| :-- | :-- |
| `<sch-base>-bom-dev.csv` | One line per group of the schematic with the dev part: `#`, `Designator`, `Qty`, `Value`, `Package`, `Tolerance` (`1 %`), `Rating` (a resistor's power, a capacitor's voltage, an IC's temperature range), `Dielectric`, `Height` (mm, where the catalog states one), `Manufacturer`, `Manufacturer PN`, `LCSC`, `Digikey`, `Catalog` (the row's id), `Status` (the catalog's word: `active`, `conditional`, `sourcing-open`; `unresolved` without a row), `Lifecycle` and `Verified` (ICs only), `Note` (what is text by nature: a condition, a difference to check, the candidate for the next board revision, the reason a line is unresolved), `DNP`. |
| `<sch-base>-bom-flight.csv` | The same lines with the flight part. |
| `<sch-base>-bom-jlcpcb.csv` | The dev build in JLCPCB's assembly format: `Comment` (the value of a passive, the MPN otherwise), `Designator`, `Footprint`, `LCSC Part #`; DNP lines left out. |
| `<sch-base>-bom-issues.csv` | Every line a grade could not resolve, and every resolved row the catalog flags: `Designator`, `Grade`, `Kind` (`unresolved`, `lifecycle`, `unverified`), `Value`, `Footprint`, `MPN`, `Reason`. |

A **passive** (a reference `R…` or `C…`) is looked up by kind, value and package: the value in R-notation or SI (`4k7`, `4.7k`, `0.1u`, `100nF`, `2u2`, `0R`, `60R4`, `20m`), the package as the imperial code in the footprint name (`R_0603_1608Metric` → `0603`; a tantalum's `CP_EIA-3528-21` → `1411`). The row of the wanted grade with role `default` and status `active` wins; `shunt` and `jumper` rows match their values; an `alternative` row is taken when there is no `default` row, and `Note` says so; a `conditional` or `sourcing-open` row is taken with its status in `Status` and the condition in `Note`; a `proposal` row is never taken. A symbol with a `Manufacturer PN` that is itself a released catalog row of the wanted grade takes that row. A DNP line is resolved like any other (a part left off the dev build may be fitted in flight) and marked in the `DNP` column; only the JLCPCB file leaves it out. An unresolved line has `Status` `unresolved`, the reason in `Note`, and keeps the schematic's value, so the file is complete even when the catalog is not.

An **IC or part** (any other reference with a `Manufacturer PN`) is looked up by that number, in the ICs first and the other parts second. For the dev build it is the schematic's part with the catalog's LCSC and DigiKey numbers (an `alternative` row says so). For the flight build the slot's `flight` row replaces it when its `compat` is `drop-in`; with `drop-in-behavior` it replaces it and `Note` carries the catalog's `difference` to check; with `footprint-only` or `different-footprint` the board has to change first, so the reference part stays and `Note` names the candidate for the next board revision. A reference part that is itself qualified (`aec-q100`, `aec-q101`, `aec-q102`, `aec-q200`, `enhanced-product`, `space`) stays in the flight build, with the slot's flight row named in `Note` when there is one (the catalog's rule 3); so does one whose qualification is `accepted` – a connector, a spacer, a part with no qualified variant that is fitted to flight builds by decision –, the same way, with `Note` `accepted reference stays`; a slot with neither goes to the issues list. A symbol that already carries the slot's flight part keeps it. An IC row's `lifecycle` and `verified` are columns of their own; a row with `nrnd` or `verified` false is taken and listed in the issues file as flagged, an `obsolete` row is refused like a part the catalog does not have (the catalog's rules 4 and 5). A number neither file knows, and a symbol without `Manufacturer PN` that is not a resistor or capacitor (a switch, a connector), is an issue in both grades.

The ✓ line counts: `9/11 dev, 8/11 flight resolved, 5 issues, 3 without LCSC` (`2 flagged` joins when there are any) – issues are lines without a row, flagged are resolved rows the catalog marks `nrnd` or unverified, and the last are dev lines in the JLCPCB file without an LCSC number. The columns the stage reads are `grade`, `value`, `package`, `role`, `status`, `manufacturer`, `mpn`, `lcsc`, `digikey`, `notes`, `tolerance`, `power_w` or `voltage_v`, `dielectric`, `height_max_mm` of a passive and `temp_min_c`, `temp_max_c`, `slot`, `role`, `compat`, `qualification`, `lifecycle`, `verified`, `manufacturer`, `mpn`, `lcsc`, `digikey`, `difference` of an IC; a file missing one of the required columns, or a folder without its files, stops the run before the first project. The resolution export goes to `.work/bom-resolve.csv` and is removed with the work folder (kept with `--debug`).

### 5.1 Build and Qty per footprint

Two symbol fields shape the lines. **`Build`** – `dev` or `flight` – says a part is fitted in that build only (the EPS module landing headers `61300811821`, dev only; flight modules are soldered directly); a symbol without it is in both. In the other build's BOM the line is marked `DNP` with `dev build only – not fitted in flight` in `Note`, not resolved for that build and not an issue there (the ✓ line counts it as `not fitted` and takes it out of that build's denominator), and the JLCPCB file (the dev build) leaves out a flight-only part; any other value is a usage error naming the reference. **`Qty per footprint`** says how many parts one placed footprint takes (the EPS module landing pad carries `4` for its four 1 × 8 sockets); the quantities of the plain export and the build BOMs are multiplied by it (J401 + J601 → 8 × `61300811821`), the JLCPCB file lists designators and is not. Empty means 1; anything that is not a whole number is a usage error naming the reference. The plain export reads the field through a trailing column the stage adds and removes again, so `[bom] fields` need not name it.

### 5.2 The frozen project

The thin project leaves the part choice to the catalogs, which is right while a board is in development. For a release, an assembler or an archive, `--freeze dev` or `--freeze flight` writes `<project>-frozen-<build>/` next to the project folder (a sibling, so `${KIPRJMOD}/..` library paths keep working): a copy of the folder without backups, caches and lock files, in which every placed symbol and every board footprint whose line the build resolves carries `Manufacturer PN`, `LCSC` and `Digikey` (existing fields are set, missing ones added hidden after the last property; no "Update PCB from Schematic" needed), `Value` stays as the designer wrote it, and a part the `Build` field keeps out of the build gets KiCad's DNP attribute in the sheet and on the board. The first two free comment slots of every title block take `Frozen flight build 2026-11-05 (bac-kicad-generate-artifacts 0.8.0)` and `Catalogs passives 0.3.7, ics 0.5.1, other 0.5.1; source d0923075` (the catalog versions from the folders' README histories, the commit from `git rev-parse` with `+` when the tree is dirty, `unknown` without git); `FROZEN.md` next to the project files repeats them with the lines that stayed unresolved, the rows the catalog flags, the parts not fitted and the references resolved in the schematic but missing on the board. The ✓ line counts symbols and footprints written, parts DNP by `Build` and unresolved lines. A folder of that name from an earlier run is replaced; one open in KiCad (a lock file) stops the stage. The stage needs the thin scheme and the catalogs (a run without them, or `--only freeze` without `--freeze`, is a usage error before the first project; `--freeze` with a stage list that leaves `freeze` out is warned about); it runs its own resolution export, so `--only freeze` works on its own. A frozen folder is not accepted as a source. Sheets whose title block has no two free comment slots are listed in `FROZEN.md`. An `R…`/`C…` line the passives catalog does not match but whose `Manufacturer PN` the ICs or other-parts file knows (an NTC, a resistor network) resolves through that number.

### 5.3 The legacy scheme

A project from before the catalogs – the symbols carry `Manufacturer`, `Manufacturer PN`, `Package`, `Tolerance`, `R Rated Power`, `C Class`, `C D Rated Voltage` and `Notes` themselves – runs with `--bom-scheme legacy` (or `scheme = "legacy"` in `[bom]`): the plain export has the 0.7 columns (`#`, `Designator`, `Qty`, `Manufacturer`, `Manufacturer PN`, `Value`, `Package`, `Tolerance`, `R Rated Power`, `C Class`, `C D Rated Voltage`, `Notes`, `DNP`, `Digikey URL`; `Alternative parts` is gone), no catalog is read, and the dev, flight, JLCPCB and issues files are not written; `--freeze` is refused. A thin-scheme run on a project whose sheets carry `C Class` or `R Rated Power` prints a hint. The interactive BOM and the centroid file read KiCad's DNP attribute in both schemes, so a legacy project's `BOM` and `DNP` fields no longer matter. An explicit `fields`/`labels`/`group_by` in `[bom]` overrides the scheme's columns either way.

## 6. QR code

Place a square text box (`gr_text_box`) with the text `QR_MARKER` on the board where the code should go, on any layer. With `--qr TEXT` (or `text` in `[qr]`) the `qr` stage replaces every such box with the QR code for the text: one filled zero-width `gr_rect` per dark module, the module size the box's side divided by the code's size, error correction level L, the smallest version that holds the text, no quiet zone (leave room around the box). On a back layer the code is mirrored left to right so it reads correctly when the board is turned over. A box that is not square gets the code centred in the square of its shorter side. `${TITLE}`, `${REVISION}`, `${COMPANY}`, `${ISSUE_DATE}` and `${COMMENT1}` … `${COMMENT9}` in the text are replaced from the board's title block, so `--qr '${COMMENT4}'` encodes the bac.page link the deployment switch carries in its fourth comment.

The stage works on a copy of the project folder in `.work/project/` (backups, lock files and caches left out) and the later board stages of the same run export from that copy, so the render, Gerbers and STEP carry the code while the project itself is untouched; the copy is removed with `.work/` at the end of the project (kept with `--debug`, ignored by the next run). A box must sit at 0° or 180°; a rotated one is an error. When the modules come out smaller than 0.2 mm the ✓ line says so, since most fabs cannot print finer silkscreen. 3D model paths relative to `${KIPRJMOD}` resolve inside the copy, so models stored next to the project are found; models referenced relative to a folder outside the project are not. No board of the Build a CubeSat project carries a marker yet; the deployment switch fixture under `tests/fixtures/` does.

The stage is a reimplementation of Emil Fresk's [kicad-qr-inserter](https://github.com/korken89/kicad-qr-inserter) (MIT), which does the same with the `pcbnew` Python module. This version reads and edits the board through `bac_common.sexp`, so it needs no KiCad Python and changes nothing in the file but the marker boxes.

## 7. Fixtures and tests

`tests/fixtures/deployment-switch/kicad10/` is the BAC deployment switch (KiCad 10 format, one sheet, two footprints, 4.8 × 8.7 mm) with a `QR_MARKER` text box added on `B.SilkS`; it is the live fixture for a run with the installed KiCad. `tests/fixtures/eps/` holds a hand-written four-layer project with renamed inner layers, a hierarchical sheet and two marker boxes, and a schematic-less copy of it as a panel with a V-cut line on `User.Comments`. `kicad-cli` is not needed to run the tests: a stand-in runner writes the files each subcommand would produce. The 129 tests cover the title block and version tags, the naming, the layer map and the rename pass including the job file, the QR geometry front and back, every stage, the command line and the config, the build BOMs with `Build` and `Qty per footprint`, the two schemes and the frozen project (the catalog reader's own 49 tests are in `bac-common`). The synthetic project places two resistors, a CAN transceiver and a module landing pad (`Build` `dev`, `Qty per footprint` `4`) for the BOM and freeze tests.

A run on the deployment switch with kicad-cli present looks like this:

```sh
bac-kicad-generate-artifacts --desktop ~/Desktop/releases --qr '${COMMENT4}' tests/fixtures/deployment-switch/kicad10
```

## 8. Changes against 0.4.2 and 0.5.0

0.6.0 merges the two earlier lines: the stage architecture, `--only`/`--skip` and the parsing tests of the 0.5.0 candidate of 2026-05, and the behaviour of the installed 0.4.2 (panel mode, the rename pass, UTC timestamps, dry run, summary). On top of that: the package moves onto `bac-common` (Rich output, standard flags, config and `--init`, error boundary); the output folder and the artifacts are named after the project's own name instead of the parent folder (`adcs/magnetorquer-placeholder-XY/1U/kicad9` was `bac-adcs-1U-…`) and the prefix no longer doubles; renamed layers no longer leave spaces in Gerber names; the `.gbrjob` file is rewritten with the renamed paths; the stem is removed from the front of a file name only; collisions count up instead of clobbering `-dup`; a dry run creates nothing; kicad-cli's help text is no longer probed (10.x is the target); the STEP header carries name, author and organisation; `--open` replaces the unconditional launch of the file manager and GerbView; `--patch` replaces `--pcb-patch-rev` and `--schematic-patch-rev`; panel mode proceeds after its warning instead of prompting (`-y` is gone); `--keep-work` is gone, `--debug` keeps the work folder; the iBOM plugin path and interpreter come from the config instead of `--ibom-script` and `--ibom-python`, and the plugin runs with `--no-browser` unless `--open`; a project outside the hardware repository gets no subsystem instead of `unknown`; the WebP encoder is Pillow instead of `cwebp`; a failing stage prints a ✗ line on stdout and marks the project but the remaining stages still run (the top-level `ERROR` line is still stderr); the `kicad` launcher is no longer tried when `gerbview` is missing; `gerber/`, `drill/` and `centroid/` are emptied before an export and the STEP export passes `--force`, so a re-run replaces instead of accumulating. The QR stage is new.

## 9. Development

```sh
uv run pytest tools/bac-kicad-generate-artifacts
uv run ruff check tools/bac-kicad-generate-artifacts
```

Modules: `cli` (parser, the per-project loop, output), `project` (discovery, title block, tags, names, layers, the rename pass), `stages` (the twelve stages and their selection), `bom` (the resolution export, `Build` and `Qty per footprint`, the four build files), `freeze` (the frozen project: the copy, the fields by span, the DNP attribute, the title-block comments, `FROZEN.md`), `qr` (marker search and rectangle generation on `bac_common.sexp`), `runner` (program discovery, the subprocess wrapper with dry run and timeout), `config` (settings and the `--init` template).

## 10. Adapting for your own project

Set `prefix` and `hardware_root` in `[naming]` to your organisation's prefix and the name of the folder your hardware projects live under, or leave `hardware_root` pointing at a folder that does not exist to get `<prefix>-<name>-<vXrY>` without a subsystem. Put your name and organisation into `[metadata]`. Set `scheme` in `[bom]` to `legacy` if your symbols carry their part data, or replace the field list with the symbol fields your library uses (`${ITEM_NUMBER}`, `${QUANTITY}` and `${DNP}` are KiCad's built-in columns). Leave `[catalog]` empty unless you keep part collections in the shape of §5; the resolver reads `Value`, `Footprint`, `Manufacturer PN`, `Build` and `Qty per footprint`, so a library that names the MPN field differently needs `RESOLVE_FIELDS` in `bom.py` changed; the frozen project writes `Manufacturer PN`, `LCSC` and `Digikey` (`FIELDS` in `freeze.py`). Boards whose title reads `<something> v<N>` with a numeric `rev` get clean `vXrY` tags; anything else still works but produces `r-<text>` or `v-unknownr-unknown`. The render camera and the pinout layers are constants at the top of `stages.py`.

## 11. License

MIT, like the rest of bac-utils. The QR stage follows Emil Fresk's kicad-qr-inserter (MIT, © 2024 Emil Fresk) in its approach; no code of it is included.

## 12. Version history

| Version | Date | Change |
| :-- | :-- | :-- |
| 0.8.0 | 2026-11-05 | The BOM scheme: `thin` (the default; the plain export has the templates' columns plus `Build`) and `legacy` for projects whose symbols carry their part data (`[bom] scheme`, `--bom-scheme`; no catalog resolution, `--freeze` refused, a hint on a thin run that meets legacy fields; §5.3). The `Build` field (`dev`/`flight`, absent = both) and `Qty per footprint` (quantities multiplied, a non-integer is a usage error naming the reference; §5.1). The `freeze` stage: `--freeze dev|flight` writes `<project>-frozen-<build>/` next to the project with `Manufacturer PN`, `LCSC` and `Digikey` on every resolved symbol and footprint, the DNP attribute on `Build`-excluded parts, two title-block comments and `FROZEN.md` (§5.2). The interactive BOM reads KiCad's DNP attribute instead of the `BOM` field. The catalog reader and resolver moved to `bac_common.catalog`; the third collection is `other` (`[catalog] other`, `bac-other.csv`, `resources/catalog/{passives,ics,other}`; the key `parts` is read once more with a warning). `examples/catalog/other/` renamed, the `TMUX1309ABQBR` reference and the `61300811821` socket rows added; 129 tests here, the catalog's 49 in `bac-common`. |
| 0.7.2 | 2026-10-29 | A catalog row with `qualification` `accepted` – a connector, switch or spacer with no qualified variant, fitted to flight builds by decision – stays in the flight build like a qualified one, with `Note` `accepted reference stays`, so its flight issue closes per decision; `aec-q102` (LEDs) counts as qualified. The example parts rows follow the verified catalog. |
| 0.7.1 | 2026-10-28 | `[catalog] parts` names a third collection, `bac-parts.csv` in the ICs' columns, for the connectors, switches, LEDs, holders, spacers, crystals and discretes a board carries; resolved by the IC rules after the ICs. From the first live run on the MCU carrier: every passive and IC resolved, the nine remaining dev issues were exactly these. |
| 0.7.0 | 2026-10-28 | The `bom` stage resolves the schematic against the part catalogs (§5): `[catalog]` names the folders of `bac-passives-*.csv` and `bac-ics.csv`, a second export with fixed columns is matched by value and package (passives) or manufacturer part number (ICs, by slot and compatibility), and `…-bom-dev.csv`, `…-bom-flight.csv`, `…-bom-jlcpcb.csv` and `…-bom-issues.csv` are written next to the unchanged plain export. Without `[catalog]` nothing changes. `examples/catalog/` with a dozen rows; 50 new tests. |
| 0.6.2 | 2026-10-24 | The `--qr` example in the README names the live short link, `bac.page/deployment-switch-v1` (`dsw-v1` never existed); the `--help` epilog's example encodes `${COMMENT4}`, the title-block comment the deployment switch keeps its link in. No change to the tool. |
| 0.6.1 | 2026-10-07 | The output folder is named like the artifacts (`bac-inhibit-deployment-switch-v1r1/`, was `deployment-switch-v1r1/`), so two projects of one name in different subsystems no longer share a folder. From the first live run: the iBOM plugin gets absolute paths (it resolves `--dest-dir` against the board's folder), the program lookup happens at call time, `--init` keeps its `[table]` names. |
| 0.6.0 | 2026-10-06 | Rebuilt on `bac-common` as `tools/bac-kicad-generate-artifacts` in bac-utils, merging the 0.5.0 architecture with the 0.4.2 behaviour (§8). New: the `qr` stage, STEP header metadata, `--open`, `--patch`, `--init`/`--config`, the name from the project stem, Gerber names without spaces, `.gbrjob` rewrite, kicad-cli 10 targeted directly, Pillow instead of `cwebp`. Fixtures: the deployment switch and a synthetic project with a panel; 110 tests. |
| 0.5.0 | 2026-05 | Candidate (never installed): `Config`, `Runner`, `Plan` and `Stage` architecture, `--only`/`--skip`/`--verbose`, 48 tests of the pure functions. |
| 0.4.2 | 2026-08-06 | Panelized boards: also skip the pinout WebP export. |
| 0.4.1 | 2026-08-06 | Panelized boards: include the `User.Comments` layer in the Gerber export (V-cut lines). |
| 0.4.0 | 2026-08-06 | Guideline alignment: `-v`/`--version`, `--dry-run`, hidden `--debug`, semantic glyphs instead of emojis, errors to stderr, run summary, UTC hyphenated ZIP timestamp, branded header, `pyproject.toml` packaging. Panelized-board detection with confirmation prompt (`--yes` bypass) and explicit no-re-pour guard on Gerber export. Gerber/drill files renamed to the BAC artifact scheme. |
| 0.3.x | – | Prior iterations: multi-directory processing, iBOM export, patch-revision flags, centroid and STEP export. |

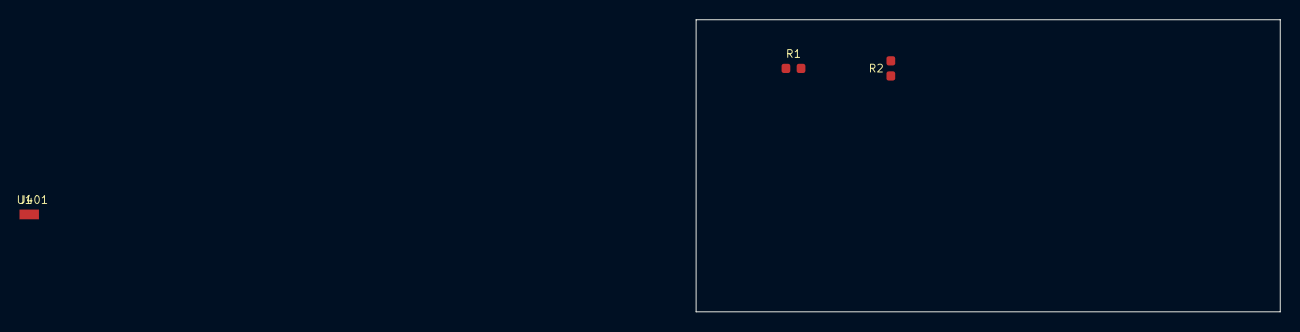
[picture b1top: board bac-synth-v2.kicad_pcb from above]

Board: 4 copper layers, 60.0 x 30.0 mm, 4 parts (0 on the bottom side), 2 nets, no tracks yet.

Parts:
J401: Landing pad; EPS-Module-Landing-Pad
R1, R2: 100k; R_0603_1608Metric
U1: TI TCAN334G; SOT-23-8

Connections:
GND: R1.1, R2.1
VCC: R1.2, R2.2
